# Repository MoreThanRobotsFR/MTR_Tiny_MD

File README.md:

# MTR_Tiny_MD
<p align="center">

</p>

# Changelog

This changelog provides a summary of the updates and changes made to the Motor Driver - MTR Tiny Motor Driver.

## Revision History:

- Rev: 1.0.3 Date: 20/03/2023
    - Update: Stepper motor controller board
    - Update: Brushless motor controller board

- Rev: 1.1.0 Date: 10/05/2023
    - Update: Overview Board w/ BLDC + Support

- Rev: 1.2.0 Date: 14/09/2023
    - Update: Power Delivery controller
    - Update: Correct SPI wrong connection
    - Update: Update net design (power net)
    - Update: Rx & Tx pinout can be used for CAN

- Rev: 1.2.2 Date: 20/09/2023
    - Update: Add low pass filter for Reset button

# Overview

<p align="center">
    
    <br>
    <em>Front</em>
</p>

<p align="center">
    
    <br>
    <em>Back</em>
</p>

**Note:** 
- Please refer to the [schematic](Docs/MTR_Tiny_MD.pdf) for detailed information about the MTR Tiny Motor Driver.
- Please refer to the [presentation](Docs/MTR_MD.pdf) for detailed information about the MTR Tiny Motor Driver.
- Please refer to the [bill of materials](Hardware/MTR_Tiny_MD/bom/bom.html) for detailed information about the MTR Tiny Motor Driver.

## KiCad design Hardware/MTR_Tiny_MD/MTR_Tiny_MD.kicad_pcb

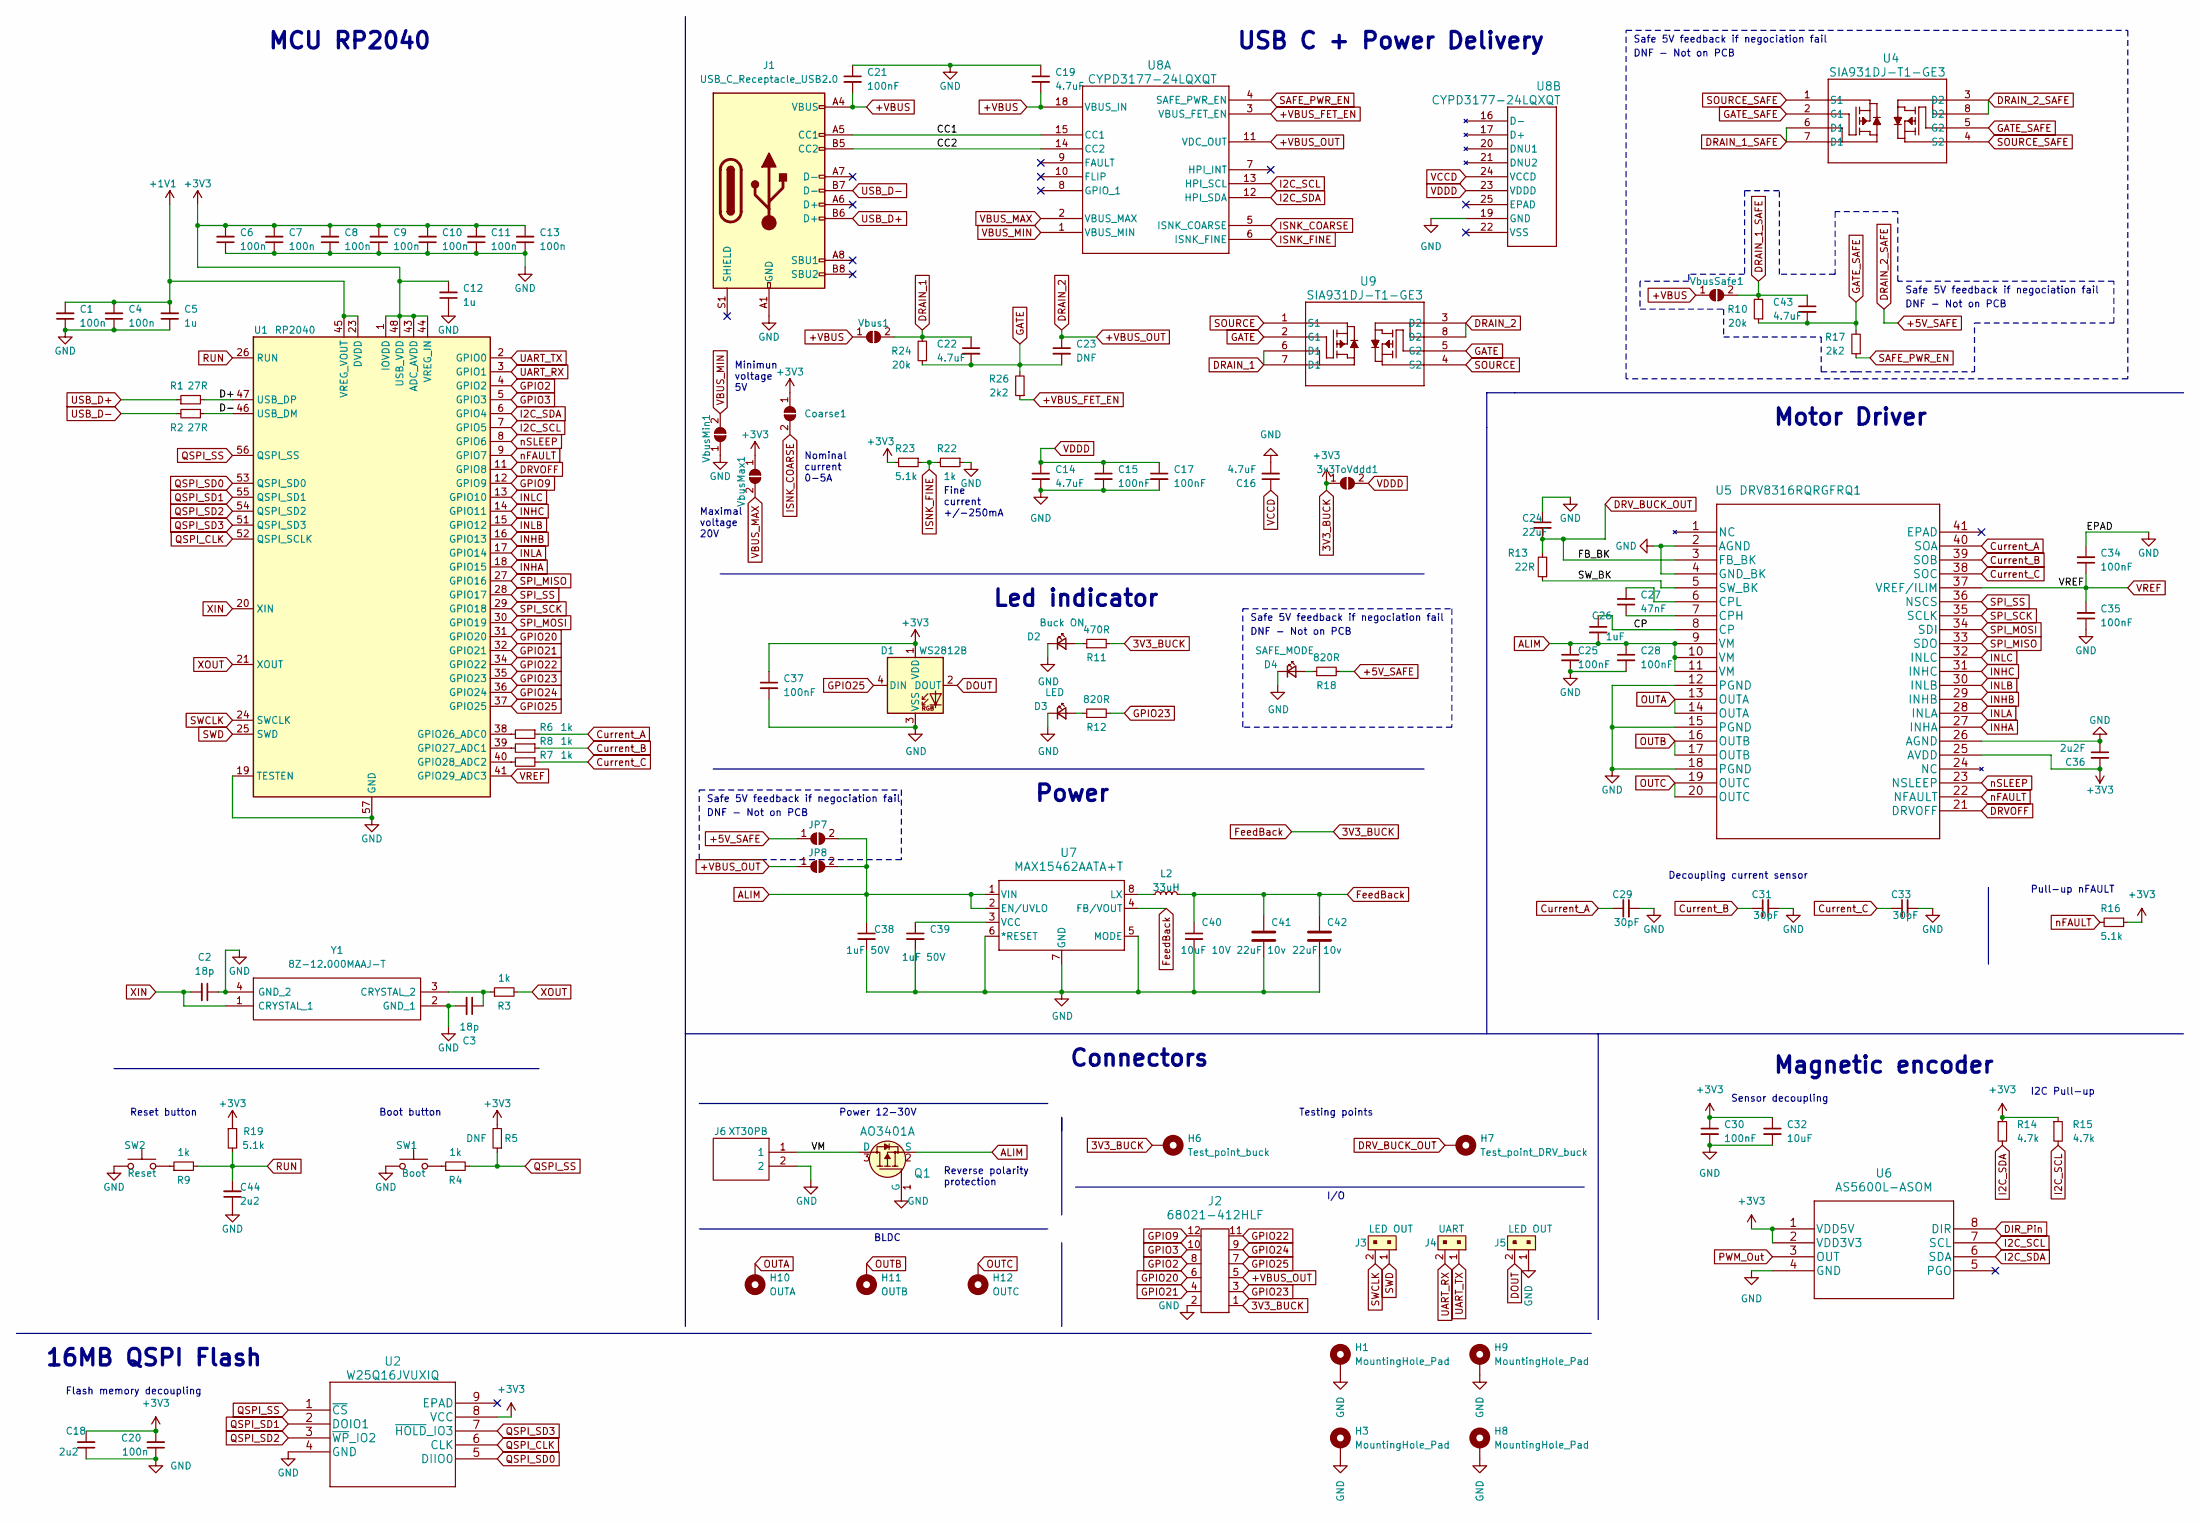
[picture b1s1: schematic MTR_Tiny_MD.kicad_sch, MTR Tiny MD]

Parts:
3v3ToVddd1: 3V3toVddJumper; R_0201_0603Metric
C1, C4, C6, C7, C8, C9, C10, C11, C13, C20: 100n; C_0402_1005Metric
C2, C3: 18p; C_0402_1005Metric
C5: 1u; C_0402_1005Metric
C12: 1u; C_0603_1608Metric
C14, C16, C19, C22, C43: 4.7uF; C_0402_1005Metric
C15, C17, C21, C30, C34, C35: 100nF; C_0402_1005Metric
C18, C44: 2u2; C_0402_1005Metric
C23: DNF; C_0402_1005Metric
C24: 22uF; C_0603_1608Metric
C25, C28, C37: 100nF; C_0603_1608Metric
C26: 1uF; C_0603_1608Metric
C27: 47nF; C_0603_1608Metric
C29, C31, C33: 30pF; C_0201_0603Metric
C32: 10uF; C_0402_1005Metric
C36: 2u2F; C_0603_1608Metric
C38, C39: 1uF 50V; C_1206_3216Metric
C40: 10uF 10V; C_1206_3216Metric
C41, C42: 22uF 10v; C_0603_1608Metric
Coarse1: CurrentSelect; R_0201_0603Metric
D1: WS2812B; LED_WS2812B_PLCC4_5.0x5.0mm_P3.2mm
D2: Buck ON; LED_0603_1608Metric
D3: LED; LED_0603_1608Metric
D4: SAFE_MODE; LED_0603_1608Metric
H1, H3, H8, H9: MountingHole_Pad; MountingHole_3.2mm_M3_Pad_Via
H6: Test_point_buck; TestPoint_Pad_D1.0mm
H7: Test_point_DRV_buck; TestPoint_Pad_D1.0mm
H10: OUTA; Motor_Wire_Solder_Pad
H11: OUTB; Motor_Wire_Solder_Pad
H12: OUTC; Motor_Wire_Solder_Pad
J1: USB_C_Receptacle_USB2.0; USB_C_Receptacle_HRO_TYPE-C-31-M-12
J2: 68021-412HLF; PinHeader_2x06_P2.54mm_Vertical; MPN 68021-412HLF; Digi-Key_PN 609-3355-ND
J3, J5: LED OUT; PinHeader_1x02_P2.54mm_Vertical; MPN 22-23-2021; Digi-Key_PN WM4200-ND
J4: UART; PinHeader_1x02_P2.54mm_Vertical; MPN 22-23-2021; Digi-Key_PN WM4200-ND
J6: XT30PB; CONN_XT30UPB-M_AMA; Manufacturer_Part_Number XT30PB
JP7: +5V_SAFE; R_0201_0603Metric
JP8: +VBUS_OUT; R_0201_0603Metric
L2: 33uH; L_1210_3225Metric
Q1: AO3401A; SOT-23-3; MPN AO3401A; Digi-Key_PN 785-1001-1-ND
R1, R2: 27R; R_0402_1005Metric
R3, R4, R6, R7, R8, R9, R22: 1k; R_0402_1005Metric
R5: DNF; R_0402_1005Metric
R10, R24: 20k; R_0402_1005Metric
R11: 470R; R_0402_1005Metric
R12, R18: 820R; R_0402_1005Metric
R13: 22R; R_0603_1608Metric
R14, R15: 4.7k; R_0402_1005Metric
R16, R19, R23: 5.1k; R_0402_1005Metric
R17, R26: 2k2; R_0402_1005Metric
SW1: Boot; TVAF06-A020B-R
SW2: Reset; TVAF06-A020B-R
U1: RP2040; QFN-56-1EP_7x7mm_P0.4mm_EP3.2x3.2mm
U2: W25Q16JVUXIQ
U4, U9: SIA931DJ-T1-GE3; MOSFET_T1-GE3_VIS
U5: DRV8316RQRGFRQ1
U6: AS5600L-ASOM
U7: MAX15462AATA+T; 21-0487_T822CN&plus_1_MXM
U8: CYPD3177-24LQXQT; CYPD3177-24LQXQT_CYP
Vbus1: VbusJumper; R_0201_0603Metric
VbusMax1: VbusMax; R_0201_0603Metric
VbusMin1: VbusMin; R_0201_0603Metric
VbusSafe1: VbusJumper; R_0201_0603Metric
Y1: 8Z-12.000MAAJ-T; 8Z12000MAAJT; Manufacturer_Part_Number 8Z-12.000MAAJ-T; Mouser Part Number 717-8Z-12.000MAAJ-T

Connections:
3V3_BUCK: 3v3ToVddd1.1 (A), C6.2, C7.2, C8.2, C9.2, C10.2, C11.2, C12.2, C13.2, C18.2, C20.2, C30.1, C32.1, C36.2, C37.1, C40.1, C41.1, C42.1, Coarse1.1 (A), D1.1 (VDD), H6.1, J2.1, L2.2, R5.2, R11.2, R14.1, R15.1, R16.1, R19.1, R23.2, U1.1 (IOVDD), U1.10 (IOVDD), U1.22 (IOVDD), U1.33 (IOVDD), U1.42 (IOVDD), U1.43 (ADC_AVDD), U1.44 (VREG_IN), U1.48 (USB_VDD), U1.49 (IOVDD), U2.8 (VCC), U5.25 (AVDD), U6.1 (VDD5V), U6.2 (VDD3V3), U7.4 (FB/VOUT), VbusMax1.1 (A)
+1V1: C1.2, C4.2, C5.2, U1.23 (DVDD), U1.45 (VREG_VOUT), U1.50 (DVDD)
+VBUS: C19.2, C21.2, J1.A4 (VBUS), J1.A9 (VBUS), J1.B4 (VBUS), J1.B9 (VBUS), U8.18 (VBUS_IN), Vbus1.1 (A), VbusSafe1.1 (A)
+VBUS_FET_EN: R26.1, U8.3 (VBUS_FET_EN)
+VBUS_OUT: C23.1, J2.5, JP8.1 (A), U8.11 (VDC_OUT), U9.3 (D2), U9.8 (D2)
/CC1: J1.A5 (CC1), U8.15 (CC1)
/CC2: J1.B5 (CC2), U8.14 (CC2)
/CP: C26.1, U5.8 (CP)
/D+: R1.2, U1.47 (USB_DP)
/D-: R2.1, U1.46 (USB_DM)
/SW_BK: R13.1, U5.5 (SW_BK)
/VM: J6.1, Q1.3 (D)
ALIM: C25.1, C26.2, C28.1, C38.1, JP7.2 (B), JP8.2 (B), Q1.2 (S), U5.9 (VM), U5.10 (VM), U5.11 (VM), U7.1 (VIN), U7.2 (EN/UVLO)
Current_A: C29.1, R6.1, U5.40 (SOA)
Current_B: C31.1, R7.1, U5.39 (SOB)
Current_C: C33.1, R8.1, U5.38 (SOC)
DIR_Pin: U6.8 (DIR)
DOUT: D1.2 (DOUT), J5.2
DRAIN_1: C22.1, R24.2, U9.6 (D1), U9.7 (D1), Vbus1.2 (B)
DRVOFF: U1.11 (GPIO8), U5.21 (DRVOFF)
DRV_BUCK_OUT: C24.2, H7.1, R13.2, U5.3 (FB_BK)
GATE: C22.2, C23.2, R24.1, R26.2, U9.2 (G1), U9.5 (G2)
GND: C1.1, C2.1, C3.2, C4.1, C5.1, C6.1, C7.1, C8.1, C9.1, C10.1, C11.1, C12.1, C13.1, C14.2, C15.2, C16.2, C17.2, C18.1, C19.1, C20.1, C21.1, C24.1, C25.2, C28.2, C29.2, C30.2, C31.2, C32.2, C33.2, C34.2, C35.1, C36.1, C37.2, C38.2, C39.2, C40.2, C41.2, C42.2, C44.1, D1.3 (VSS), D2.1 (K), D3.1 (K), D4.1 (K), H1.1, H3.1, H8.1, H9.1, J1.A1 (GND), J1.A12 (GND), J1.B1 (GND), J1.B12 (GND), J2.2, J5.1, J6.2, Q1.1 (G), R22.1, SW1.1, SW2.1, U1.19 (TESTEN), U1.57 (GND), U2.4 (GND), U5.2 (AGND), U5.4 (GND_BK), U5.12 (PGND), U5.15 (PGND), U5.18 (PGND), U5.26 (AGND), U6.4 (GND), U7.5 (MODE), U7.6 (*RESET), U7.7 (GND), U8.19 (GND), VbusMin1.1 (A), Y1.2 (GND_1), Y1.4 (GND_2)
GPIO2: J2.8, U1.4 (GPIO2)
GPIO3: J2.10, U1.5 (GPIO3)
GPIO9: J2.12, U1.12 (GPIO9)
GPIO20: J2.6, U1.31 (GPIO20)
GPIO21: J2.4, U1.32 (GPIO21)
GPIO22: J2.11, U1.34 (GPIO22)
GPIO23: J2.3, R12.2, U1.35 (GPIO23)
GPIO24: J2.9, U1.36 (GPIO24)
GPIO25: D1.4 (DIN), J2.7, U1.37 (GPIO25)
I2C_SCL: R15.2, U1.7 (GPIO5), U6.7 (SCL), U8.13 (HPI_SCL)
I2C_SDA: R14.2, U1.6 (GPIO4), U6.6 (SDA), U8.12 (HPI_SDA)
INHA: U1.18 (GPIO15), U5.27 (INHA)
INHB: U1.16 (GPIO13), U5.29 (INHB)
INHC: U1.14 (GPIO11), U5.31 (INHC)
INLA: U1.17 (GPIO14), U5.28 (INLA)
INLB: U1.15 (GPIO12), U5.30 (INLB)
INLC: U1.13 (GPIO10), U5.32 (INLC)
ISNK_COARSE: Coarse1.2 (B), U8.5 (ISNK_COARSE)
ISNK_FINE: R22.2, R23.1, U8.6 (ISNK_FINE)
unnamed: C43.1, R10.2, U4.6 (D1), U4.7 (D1), VbusSafe1.2 (B)
unnamed: C43.2, R10.1, R17.2, U4.2 (G1), U4.5 (G2)
unnamed: D2.2 (A), R11.1
unnamed: D3.2 (A), R12.1
unnamed: D4.2 (A), R18.1
unnamed: JP7.1 (A), R18.2, U4.3 (D2), U4.8 (D2)
unnamed: R4.1, SW1.2
unnamed: R9.1, SW2.2
unnamed: R6.2, U1.38 (GPIO26_ADC0)
unnamed: R7.2, U1.39 (GPIO27_ADC1)
unnamed: R8.2, U1.40 (GPIO28_ADC2)
unnamed: U4.1 (S1), U4.4 (S2)
unnamed: C27.1, U5.7 (CPH)
unnamed: C27.2, U5.6 (CPL)
unnamed: L2.1, U7.8 (LX)
unnamed: C39.1, U7.3 (VCC)
unnamed: C3.1, R3.1, Y1.3 (CRYSTAL_2)
OUTA: H10.1, U5.13 (OUTA), U5.14 (OUTA)
OUTB: H11.1, U5.16 (OUTB), U5.17 (OUTB)
OUTC: H12.1, U5.19 (OUTC), U5.20 (OUTC)
PWM_Out: U6.3 (OUT)
QSPI_CLK: U1.52 (QSPI_SCLK), U2.6 (CLK)
QSPI_SD0: U1.53 (QSPI_SD0), U2.5 (DIIO0)
QSPI_SD1: U1.55 (QSPI_SD1), U2.2 (DOIO1)
QSPI_SD2: U1.54 (QSPI_SD2), U2.3 (~WP_IO2)
QSPI_SD3: U1.51 (QSPI_SD3), U2.7 (~HOLD_IO3)
QSPI_SS: R4.2, R5.1, U1.56 (QSPI_SS), U2.1 (~CS)
RUN: C44.2, R9.2, R19.2, U1.26 (RUN)
SAFE_PWR_EN: R17.1, U8.4 (SAFE_PWR_EN)
SOURCE: U9.1 (S1), U9.4 (S2)
SPI_MISO: U1.27 (GPIO16), U5.33 (SDO)
SPI_MOSI: U1.30 (GPIO19), U5.34 (SDI)
SPI_SCK: U1.29 (GPIO18), U5.35 (SCLK)
SPI_SS: U1.28 (GPIO17), U5.36 (NSCS)
SWCLK: J3.2, U1.24 (SWCLK)
SWD: J3.1, U1.25 (SWD)
UART_RX: J4.2, U1.3 (GPIO1)
UART_TX: J4.1, U1.2 (GPIO0)
USB_D+: J1.B6 (D+), R1.1
USB_D-: J1.B7 (D-), R2.2
VBUS_MAX: U8.2 (VBUS_MAX), VbusMax1.2 (B)
VBUS_MIN: U8.1 (VBUS_MIN), VbusMin1.2 (B)
VCCD: C16.1, U8.24 (VCCD)
VDDD: 3v3ToVddd1.2 (B), C14.1, C15.1, C17.1, U8.23 (VDDD)
VREF: C34.1, C35.2, U1.41 (GPIO29_ADC3), U5.37 (VREF/ILIM)
XIN: C2.2, U1.20 (XIN), Y1.1 (CRYSTAL_1)
XOUT: R3.2, U1.21 (XOUT)
nFAULT: R16.2, U1.9 (GPIO7), U5.22 (NFAULT)
nSLEEP: U1.8 (GPIO6), U5.23 (NSLEEP)

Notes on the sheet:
DNF - Not on PCB
Sensor decoupling
Safe 5V feedback if negociation fail
Minimun voltage 5V
Connectors
Fine current +/-250mA
I/O
Reverse polarity protection
USB C + Power Delivery
Power 12-30V
Reset button
MCU RP2040
Motor Driver
Nominal current 0-5A
Decoupling current sensor
Flash memory decoupling
Power
BLDC
16MB QSPI Flash
I2C Pull-up
Maximal voltage 20V
Pull-up nFAULT
Led indicator
Testing points
Magnetic encoder
Boot button

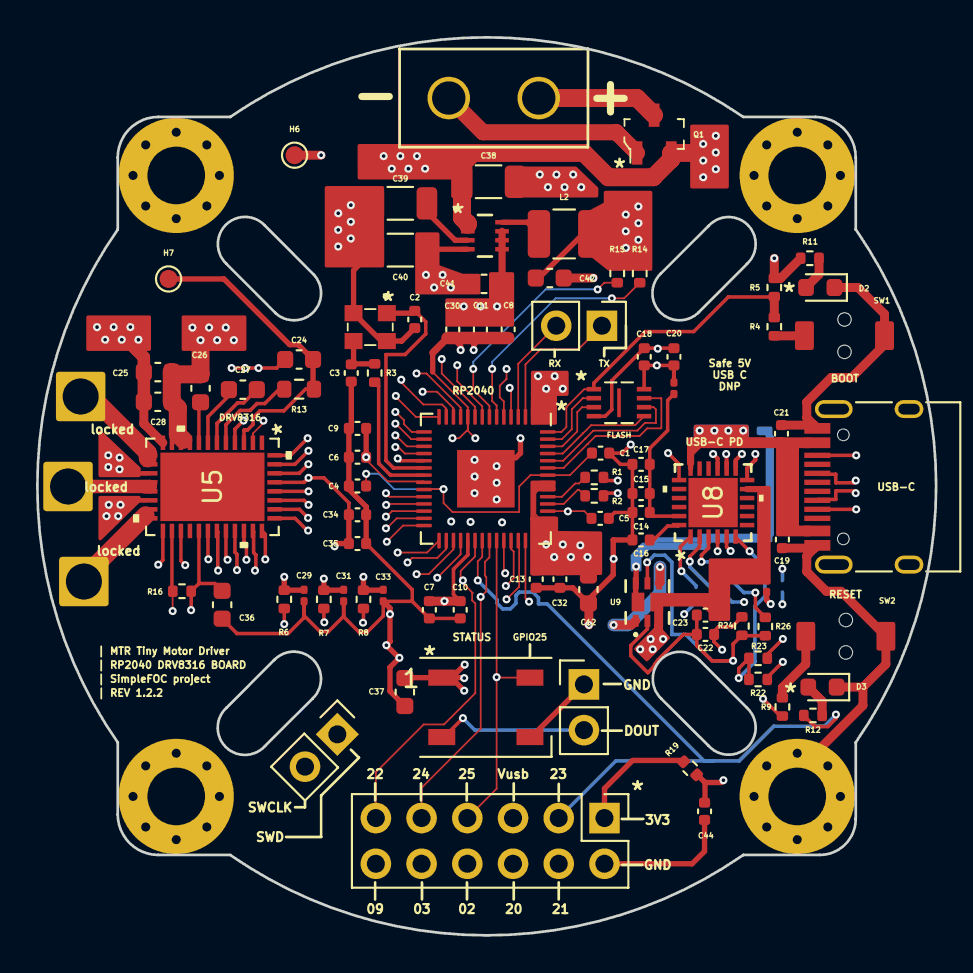
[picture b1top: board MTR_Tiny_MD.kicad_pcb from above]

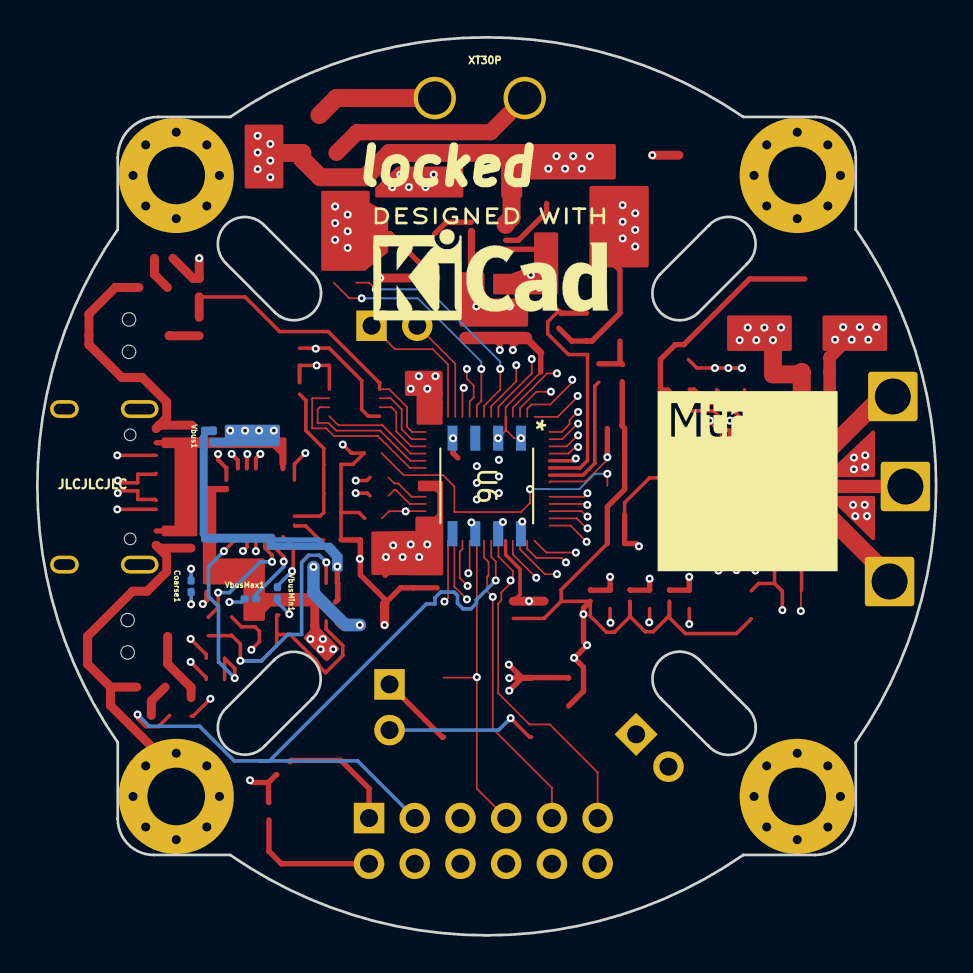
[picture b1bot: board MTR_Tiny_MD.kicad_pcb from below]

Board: 6 copper layers, 49.9 x 49.9 mm, 99 parts (5 on the bottom side), 83 nets.

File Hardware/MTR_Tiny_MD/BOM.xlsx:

Item | Qty | Reference(s) | Value | LibPart | Footprint | Datasheet
34 | 1 | Q1 | AO3401A | dk_Transistors-FETs-MOSFETs-Single:AO3401A | digikey-footprints:SOT-23-3 | http://aosmd.com/res/data_sheets/AO3401A.pdf
45 | 1 | U2 | W25Q16JVUXIQ | W25Q16JVUXIQ:W25Q16JVUXIQ | Personal:W25Q16JVUXIQ | https://www.mouser.fr/datasheet/2/949/w25q16jv_spi_revg_0322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
47 | 1 | U4 | TPS71933-33DRVR | 2023-01-28_15-38-30:TPS71933-33DRVR | Personal:TPS71933-33DRVR
49 | 1 | U6 | AS5600L-ASOM | AS5600L-ASOM:AS5600L-ASOM | Personal:AS5600L-ASOM | https://www.mouser.fr/datasheet/2/588/AS5600L_DS000545_3_00-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
50 | 1 | Y1 | 8Z-12.000MAAJ-T | SamacSys_Parts:8Z-12.000MAAJ-T | SamacSys_Parts:8Z12000MAAJT | http://www.txccrystal.com/images/pdf/8z.pdf
1 | 10 | C1, C4, C6, C7, C8, C9, C10, C11, C13, C20 | 100n | Device:C_Small | Capacitor_SMD:C_0402_1005Metric | ~
2 | 2 | C2, C3 | 18p | Device:C_Small | Capacitor_SMD:C_0402_1005Metric | ~
3 | 1 | C5 | 1u | Device:C_Small | Capacitor_SMD:C_0402_1005Metric | ~
4 | 1 | C12 | 1u | Device:C_Small | Capacitor_SMD:C_0603_1608Metric | ~
5 | 1 | C14 | 2.2uF 50v | Device:C | Capacitor_SMD:C_0805_2012Metric | ~
6 | 2 | C15, C19 | 100nF 50v | Device:C | Capacitor_SMD:C_0603_1608Metric | ~
7 | 1 | C16 | 1uF 16v | Device:C | Capacitor_SMD:C_0603_1608Metric | ~
8 | 2 | C17, C22 | 10uF | Device:C | Capacitor_SMD:C_0603_1608Metric | ~
9 | 1 | C18 | 2u2 | Device:C_Small | Capacitor_SMD:C_0402_1005Metric | ~
10 | 2 | C21, C23 | 22uF 10v | Device:C | Capacitor_SMD:C_0603_1608Metric | ~
11 | 1 | C24 | 22uF | Device:C_Small | Capacitor_SMD:C_0603_1608Metric | ~
12 | 3 | C25, C28, C37 | 100nF | Device:C_Small | Capacitor_SMD:C_0603_1608Metric | ~
13 | 1 | C26 | 1uF | Device:C_Small | Capacitor_SMD:C_0603_1608Metric | ~
14 | 1 | C27 | 47nF | Device:C_Small | Capacitor_SMD:C_0603_1608Metric | ~
15 | 3 | C29, C31, C33 | 30pF | Device:C_Small | Capacitor_SMD:C_0201_0603Metric | ~
16 | 3 | C30, C34, C35 | 100nF | Device:C_Small | Capacitor_SMD:C_0402_1005Metric | ~
17 | 1 | C32 | 10uF | Device:C_Small | Capacitor_SMD:C_0402_1005Metric | ~
18 | 1 | C36 | 1.3uF | Device:C_Small | Capacitor_SMD:C_0603_1608Metric | ~
19 | 1 | D1 | WS2812B | LED:WS2812B | LED_SMD:LED_WS2812B_PLCC4_5.0x5.0mm_P3.2mm | https://cdn-shop.adafruit.com/datasheets/WS2812B.pdf
20 | 1 | D2 | Buck ON | Device:LED_Small | LED_SMD:LED_0603_1608Metric | ~
21 | 1 | D3 | USB ON | Device:LED_Small | LED_SMD:LED_0603_1608Metric | ~
22 | 4 | H1, H3, H8, H9 | MountingHole_Pad | Mechanical:MountingHole_Pad | MountingHole:MountingHole_3.2mm_M3_Pad_Via | ~
23 | 1 | H6 | Test_point_buck | Mechanical:MountingHole_Pad | TestPoint:TestPoint_Pad_1.5x1.5mm | ~
24 | 1 | H7 | Test_point_DRV_buck | Mechanical:MountingHole_Pad | TestPoint:TestPoint_Pad_1.5x1.5mm | ~
25 | 1 | H10 | OUTA | Mechanical:MountingHole_Pad | Personal:Motor_Wire_Solder_Pad | ~
26 | 1 | H11 | OUTB | Mechanical:MountingHole_Pad | Personal:Motor_Wire_Solder_Pad | ~
27 | 1 | H12 | OUTC | Mechanical:MountingHole_Pad | Personal:Motor_Wire_Solder_Pad | ~
28 | 1 | J1 | USB_C_Receptacle_USB2.0 | Connector:USB_C_Receptacle_USB2.0 | Connector_USB:USB_C_Receptacle_HRO_TYPE-C-31-M-12 | https://www.usb.org/sites/default/files/documents/usb_type-c.zip
29 | 1 | J2 | 68021-412HLF | dk_Rectangular-Connectors-Headers-Male-Pins:68021-412HLF | PinHeader:PinHeader_2x06_P2.54mm_Vertical | https://cdn.amphenol-icc.com/media/wysiwyg/files/drawing/68020.pdf
30 | 2 | J3, J5 | LED OUT | dk_Rectangular-Connectors-Headers-Male-Pins:22-23-2021 | PinHeader:PinHeader_1x02_P2.54mm_Vertical | https://media.digikey.com/pdf/Data%20Sheets/Molex%20PDFs/A-6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
31 | 1 | J4 | UART | dk_Rectangular-Connectors-Headers-Male-Pins:22-23-2021 | PinHeader:PinHeader_1x02_P2.54mm_Vertical | https://media.digikey.com/pdf/Data%20Sheets/Molex%20PDFs/A-6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
32 | 1 | J6 | XT30PB | DriverParts:XT30PB | Personal:XT30PB | https://www.tme.eu/Document/4acc913878197f8c2e30d4b8cdc47230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
33 | 1 | L1 | 15uH | pspice:INDUCTOR | Inductor_SMD:L_1210_3225Metric | ~
35 | 2 | R1, R2 | 27R | Device:R_Small | Resistor_SMD:R_0402_1005Metric | ~
36 | 7 | R3, R4, R5, R6, R7, R8, R9 | 1k | Device:R_Small | Resistor_SMD:R_0402_1005Metric | ~
37 | 1 | R11 | 470R | Device:R_Small | Resistor_SMD:R_0402_1005Metric | ~
38 | 1 | R12 | 820R | Device:R_Small | Resistor_SMD:R_0402_1005Metric | ~
39 | 1 | R13 | 22R | Device:R_Small | Resistor_SMD:R_0603_1608Metric | ~
40 | 2 | R14, R15 | 4.7k | Device:R_Small | Resistor_SMD:R_0402_1005Metric | ~
41 | 1 | R16 | 100R | Device:R_Small | Resistor_SMD:R_0402_1005Metric | ~
42 | 1 | SW1 | Boot | Switch:SW_Push | Personal:TVBM17 | ~
43 | 1 | SW2 | Reset | Switch:SW_Push | Personal:TVBM17 | ~
44 | 1 | U1 | RP2040 | MCU_RaspberryPi:RP2040 | Package_DFN_QFN:QFN-56-1EP_7x7mm_P0.4mm_EP3.2x3.2mm | https://datasheets.raspberrypi.com/rp2040/rp2040-datasheet.pdf
46 | 1 | U3 | LMR36506 | DriverParts:LMR36506 | Personal:LMR36506 | https://www.ti.com/lit/ds/symlink/lmr36506.pdf
48 | 1 | U5 | DRV8316RQRGFRQ1 | DVR8316R:DRV8316RQRGFRQ1 | Personal:DRV8316RQRGFRQ1 | https://www.ti.com/lit/ds/symlink/drv8316-q1.pdf?ts=1674332352245

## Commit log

2023-02-26 new DCDC convert
2023-03-20 add drawing.io and footprint & 3D model to project
2023-03-20 initial source code
2023-03-20 add some gitignore
2023-03-20 Delet some file
2023-04-29 Add new Vbuck
    LMR36506 to MAX15462AATA+T
2023-05-14 Silkscreen labelling - RFP
    Ready For Production Rev 1.1
2023-07-10 updating docs w/ Rev 1.1 images
2023-08-09 add local libraries and Neopixel hello world
2023-09-02 add usb C PD controler
2023-09-14 Update design, add PD controler, correct SPI
2023-09-14 Updated schematic
2023-09-22 New changelog
2023-09-29 libraries to libdep
2023-09-29 code still in progress

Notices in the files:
parts and their libraries:
Copyright 2021 Accelerated Designs. All rights reserved.
